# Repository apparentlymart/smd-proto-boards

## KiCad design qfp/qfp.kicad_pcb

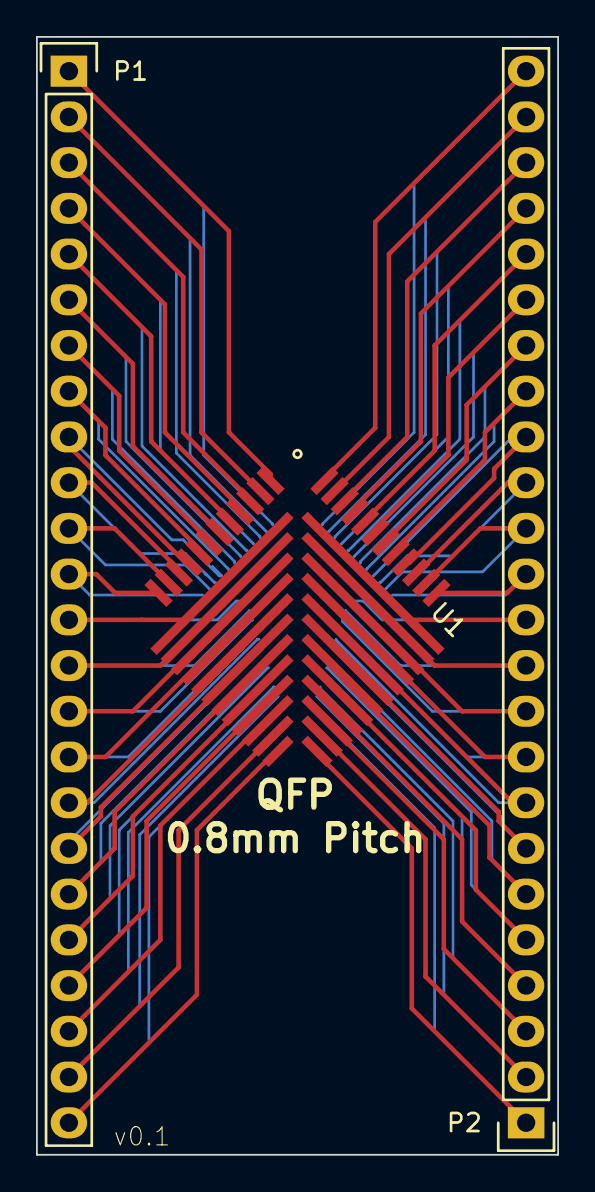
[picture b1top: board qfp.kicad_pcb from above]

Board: 2 copper layers, 29.0 x 62.1 mm, 4 parts (1 on the bottom side), 48 nets.

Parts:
P1, P2: CONN_01X24; Pin_Header_Straight_1x24
U1: QFP48; PROTOQFP
U2: TQFP48; PROTOTQFP

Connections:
PIN1: P1.1, U1.1, U2.48
PIN2: P1.2, U1.2, U2.47
PIN3: P1.3, U1.3, U2.46
PIN4: P1.4, U1.4, U2.45
PIN5: P1.5, U1.5, U2.44
PIN6: P1.6, U1.6, U2.43
PIN7: P1.7, U1.7, U2.42
PIN8: P1.8, U1.8, U2.41
PIN9: P1.9, U1.9, U2.40
PIN10: P1.10, U1.10, U2.39
PIN11: P1.11, U1.11, U2.38
PIN12: P1.12, U1.12, U2.37
PIN13: P1.13, U1.13, U2.36
PIN14: P1.14, U1.14, U2.35
PIN15: P1.15, U1.15, U2.34
PIN16: P1.16, U1.16, U2.33
PIN17: P1.17, U1.17, U2.32
PIN18: P1.18, U1.18, U2.31
PIN19: P1.19, U1.19, U2.30
PIN20: P1.20, U1.20, U2.29
PIN21: P1.21, U1.21, U2.28
PIN22: P1.22, U1.22, U2.27
PIN23: P1.23, U1.23, U2.26
PIN24: P1.24, U1.24, U2.25
PIN25: P2.1, U1.25, U2.24
PIN26: P2.2, U1.26, U2.23
PIN27: P2.3, U1.27, U2.22
PIN28: P2.4, U1.28, U2.21
PIN29: P2.5, U1.29, U2.20
PIN30: P2.6, U1.30, U2.19
PIN31: P2.7, U1.31, U2.18
PIN32: P2.8, U1.32, U2.17
PIN33: P2.9, U1.33, U2.16
PIN34: P2.10, U1.34, U2.15
PIN35: P2.11, U1.35, U2.14
PIN36: P2.12, U1.36, U2.13
PIN37: P2.13, U1.37, U2.12
PIN38: P2.14, U1.38, U2.11
PIN39: P2.15, U1.39, U2.10
PIN40: P2.16, U1.40, U2.9
PIN41: P2.17, U1.41, U2.8
PIN42: P2.18, U1.42, U2.7
PIN43: P2.19, U1.43, U2.6
PIN44: P2.20, U1.44, U2.5
PIN45: P2.21, U1.45, U2.4
PIN46: P2.22, U1.46, U2.3
PIN47: P2.23, U1.47, U2.2
PIN48: P2.24, U1.48, U2.1

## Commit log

2015-03-08 OpenSCAD sketch of the QFP land pattern.
2015-03-08 Python script to generate a kicad netlist.
    Since the pin wiring is exactly one-to-one there's little value in a
    human-readable schematic, so it's easier just to go straight to a
    machine-generated netlist which can be imported into pcbnew.
2015-03-08 Rename qfpsoic project to just "qfp".
    Originally the intent was to have a QFP on one side and SOIC on the other,
    but instead we'll now have QFP (0.8mm pitch) on one side and
    TQFP (0.5mm pitch) on the other, leaving SOIC for a separate board that
    I guess could have some sort of SOP on its reverse.
2015-03-08 kicad project file
2015-03-08 gitignores
2015-03-08 Add a PCB footprint library with a placeholder footprint.
2015-03-08 Generate footprints programmatically.
    For the moment the footprints are empty. Still need to write the logic to
    place the pads, based on the earlier OpenSCAD prototype.
2015-03-08 Build 0.8mm- and 0.5mm-pitch QFP footprints.
2015-03-08 Flip the pin assignments for 0.5mm pitch QFP.
    This footprint will be on the back of the board, so the pin assignments
    will be mirrored.
2015-03-08 Route out the 0.8mm-pitch QFP breakout.
2015-03-08 Route the 0.5mm-pitch QFP side.
2015-03-08 Add silkscreen labels.
2015-03-08 Board outline
